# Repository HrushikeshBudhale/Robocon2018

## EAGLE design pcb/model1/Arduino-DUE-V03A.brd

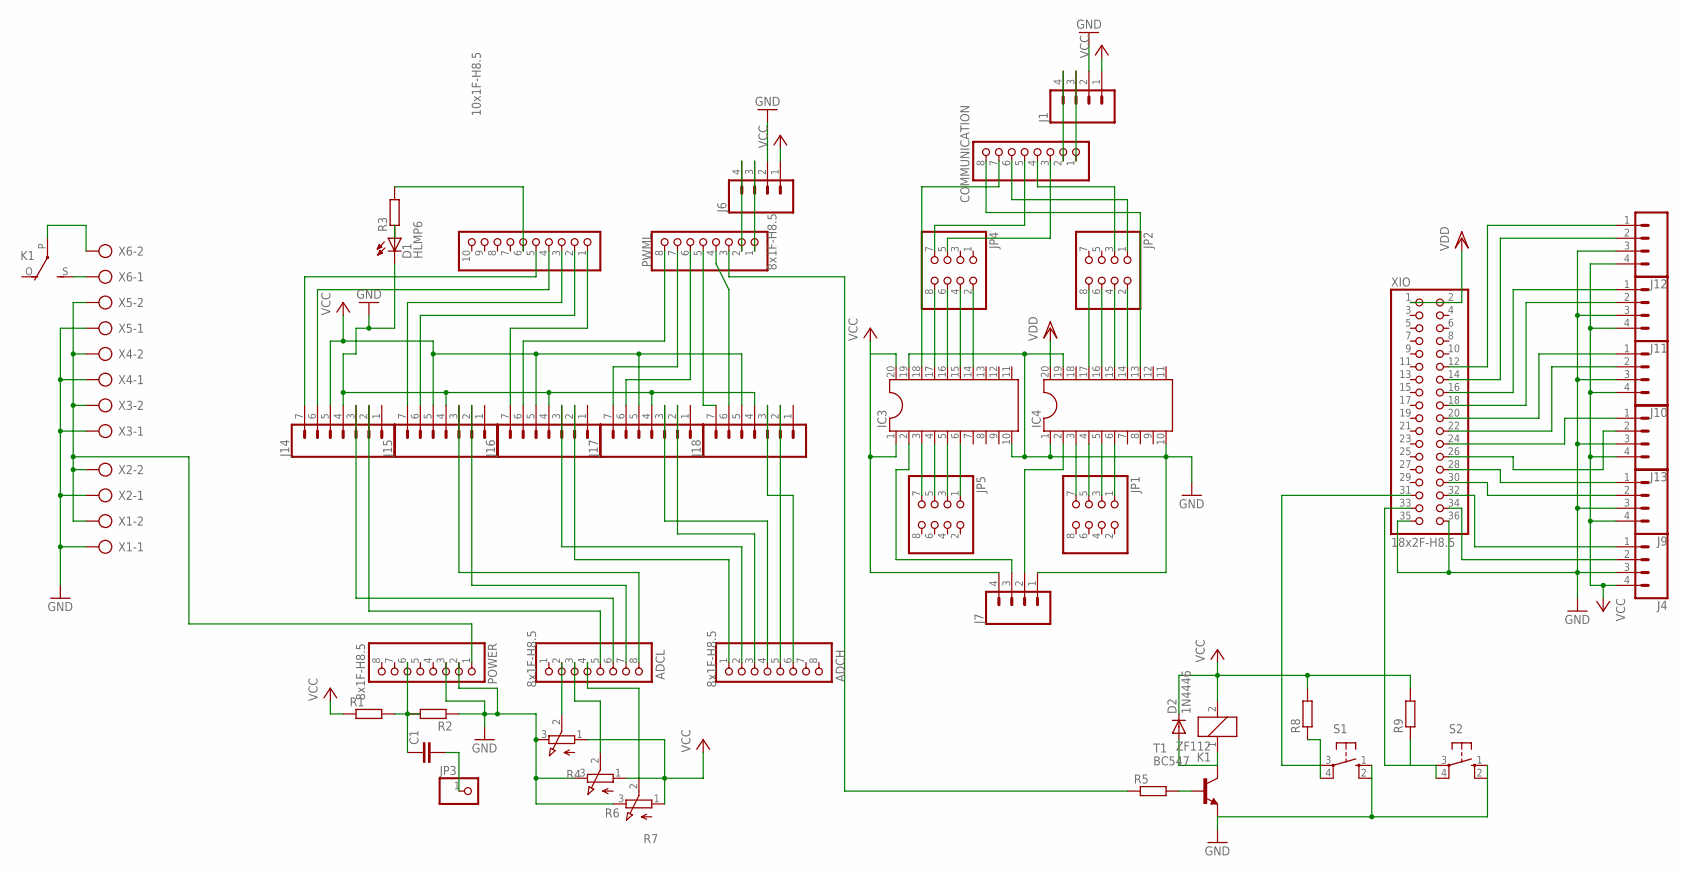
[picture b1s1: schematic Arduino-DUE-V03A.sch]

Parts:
ADCH: 8x1F-H8.5; 1X08
ADCL: 8x1F-H8.5; 1X08
C1: C-EU025-025X050; C025-025X050
COMMUNICATION: 8x1F-H8.5; 1X08
D1: HLMP6
D2: 1N4446; DO35-10
IC3, IC4: DIL20S; SOCKET-20
J1, J4, J6, J7, J9, J10, J11, J12, J13: CONN_04LONGPADS; 1X04_LONGPADS
J14, J15, J16, J17, J18: CONN_07LONGPADS; 1X07_LONGPADS
JP1, JP2, JP4, JP5: PINHD-2X4; 2X04
JP3: PINHD-1X1; 1X01
K1: ZF112
POWER: 8x1F-H8.5; 1X08
PWMH: 10x1F-H8.5; 1X10
PWML: 8x1F-H8.5; 1X08
R1, R2, R3, R5, R8, R9: R-EU_0204/7; 0204/7
R4, R6, R7: 3RP/1610N
S1, S2: 10-XX; B3F-10XX
T1: BC547; TO92
X1, X2, X3, X4, X5, X6: AK500/2
XIO: 18x2F-H8.5; 2X18

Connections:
GND: D1.K, IC3.10, IC3.19, IC4.1, IC4.10, IC4.19, J1.2, J4.3, J6.2, J7.1, J9.3, J10.3, J11.3, J12.3, J13.1, J13.3, J14.4, J15.4, J16.4, J17.4, J18.4, POWER.2, POWER.3, R2.1, R4.3 (E), R6.3 (E), R7.3 (E), S1.1 (S), S1.2 (S1), S2.1 (S), S2.2 (S1), T1.1 (E), X1.1, X2.1, X3.1, X4.1, X5.1, XIO.24, XIO.35, XIO.36
unnamed: J14.6, PWMH.4
unnamed: K1.S, X6.1
unnamed: K1.P, X6.2
unnamed: J4.2, XIO.34
unnamed: J15.6, PWMH.2
unnamed: J4.1, XIO.32
unnamed: COMMUNICATION.3, JP4.5
unnamed: J9.2, XIO.30
unnamed: J13.2, XIO.26
unnamed: POWER.1, X1.2, X2.2, X3.2, X4.2, X5.2
unnamed: J12.2, XIO.14
unnamed: J10.2, XIO.22
unnamed: J10.1, XIO.20
unnamed: J11.2, XIO.18
unnamed: J11.1, XIO.16
unnamed: J12.1, XIO.12
unnamed: R5.2, T1.2 (B)
unnamed: C1.2, JP3.1
unnamed: J16.7, PWMH.1
unnamed: J14.7, PWMH.5
unnamed: J15.7, PWMH.3
unnamed: J17.7, PWML.7
unnamed: J16.6, PWML.8
unnamed: J17.6, PWML.6
unnamed: J18.6, PWML.4
unnamed: ADCL.6, J14.3
unnamed: ADCL.5, J14.2
unnamed: ADCH.6, J18.3
unnamed: ADCH.5, J18.2
unnamed: ADCH.4, J17.3
unnamed: D1.A, R3.1
unnamed: ADCH.3, J17.2
unnamed: ADCH.2, J16.3
unnamed: ADCH.1, J16.2
unnamed: ADCL.8, J15.3
unnamed: PWMH.6, R3.2
unnamed: C1.1, POWER.6, R1.2, R2.2
unnamed: ADCL.7, J15.2
unnamed: J18.7, PWML.5
unnamed: COMMUNICATION.1, J1.3
unnamed: IC4.17, JP2.8
unnamed: IC4.16, JP2.6
unnamed: IC4.15, JP2.4
unnamed: IC4.14, JP2.2
unnamed: IC3.6, JP5.1
unnamed: IC3.5, JP5.3
unnamed: IC3.4, JP5.5
unnamed: IC3.3, JP5.7
unnamed: IC3.17, JP4.8
unnamed: IC3.16, JP4.6
unnamed: IC3.15, JP4.4
unnamed: IC3.14, JP4.2
unnamed: IC4.3, JP1.7
unnamed: IC4.4, JP1.5
unnamed: IC4.5, JP1.3
unnamed: IC4.6, JP1.1
unnamed: COMMUNICATION.7, IC3.18
unnamed: J6.4, PWML.2
unnamed: J6.3, PWML.1
unnamed: COMMUNICATION.6, JP2.1
unnamed: COMMUNICATION.2, J1.4
unnamed: COMMUNICATION.4, JP2.3
unnamed: COMMUNICATION.5, JP4.7
unnamed: IC3.2, J7.3
unnamed: IC4.2, J7.2
unnamed: D2.A, K1.1, T1.3 (C)
unnamed: R8.1, S1.3, S1.4 (P1), XIO.31
unnamed: ADCL.2, R4.2 (S)
unnamed: ADCL.4, R7.2 (S)
unnamed: ADCL.3, R6.2 (S)
unnamed: PWML.3, R5.1
unnamed: R9.1, S2.3, S2.4 (P1), XIO.33
unnamed: J9.1, XIO.28
unnamed: COMMUNICATION.8, IC4.13
VCC: D2.C, IC3.1, IC3.20, J1.1, J4.4, J6.1, J7.4, J9.4, J10.4, J11.4, J12.4, J13.4, J14.5, J15.5, J16.5, J17.5, J18.5, K1.2, R1.1, R4.1 (A), R6.1 (A), R7.1 (A), R8.2, R9.2
VDD: IC4.20, XIO.1, XIO.2

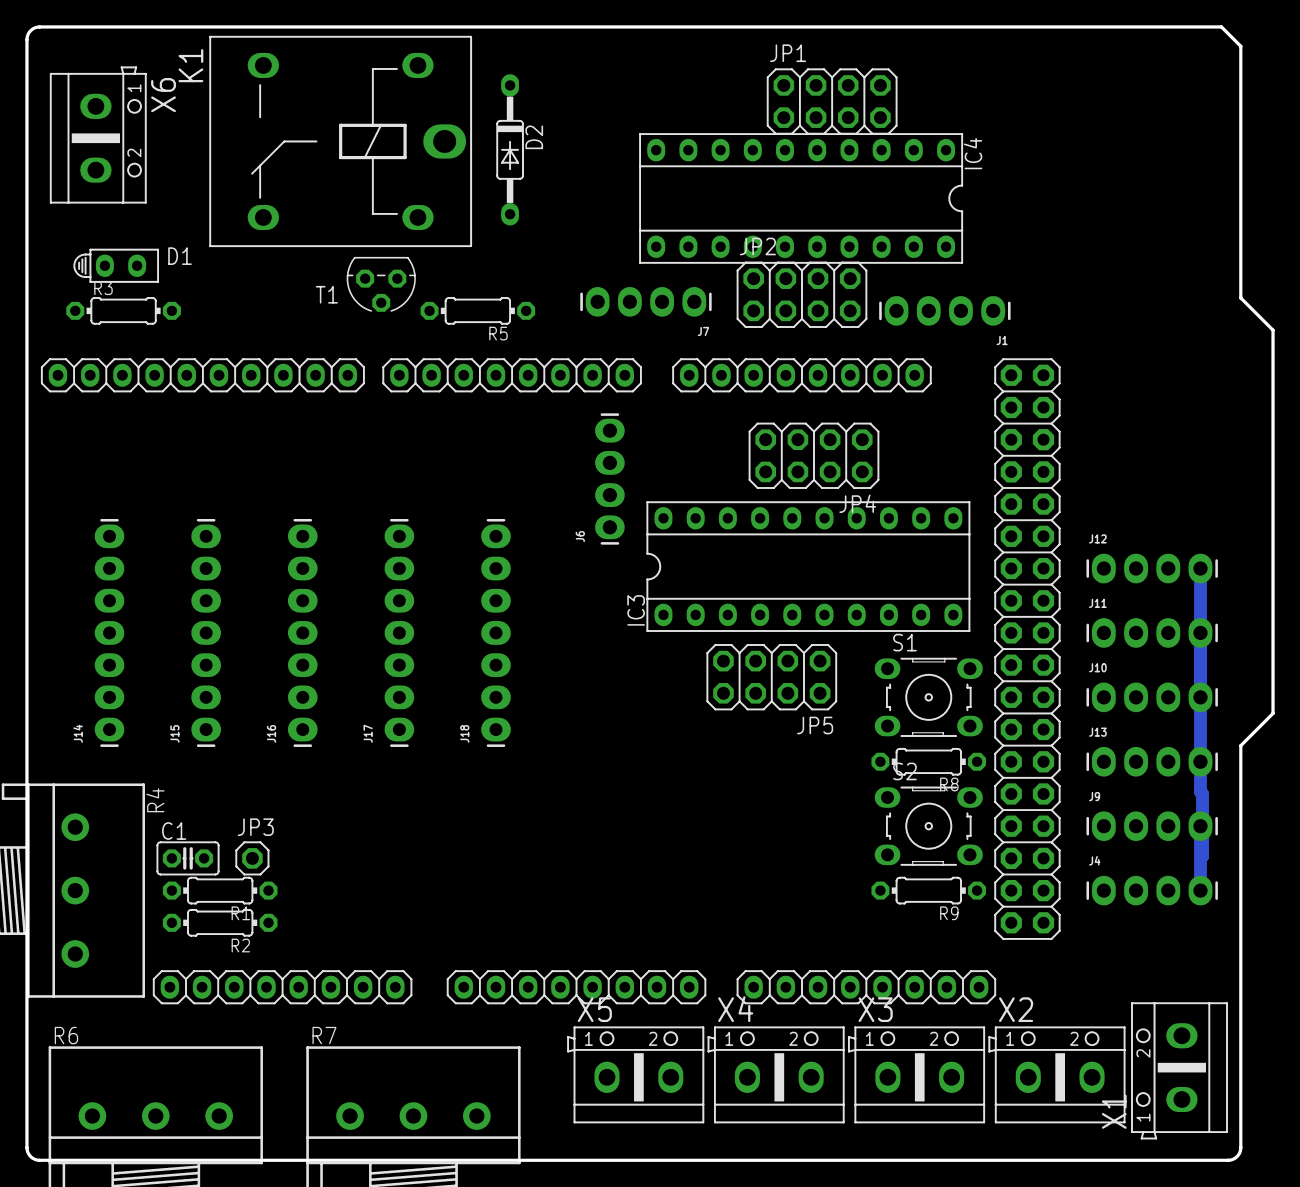
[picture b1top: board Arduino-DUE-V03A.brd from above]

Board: 2 copper layers, 98.3 x 89.4 mm, 50 parts (0 on the bottom side), 77 nets.

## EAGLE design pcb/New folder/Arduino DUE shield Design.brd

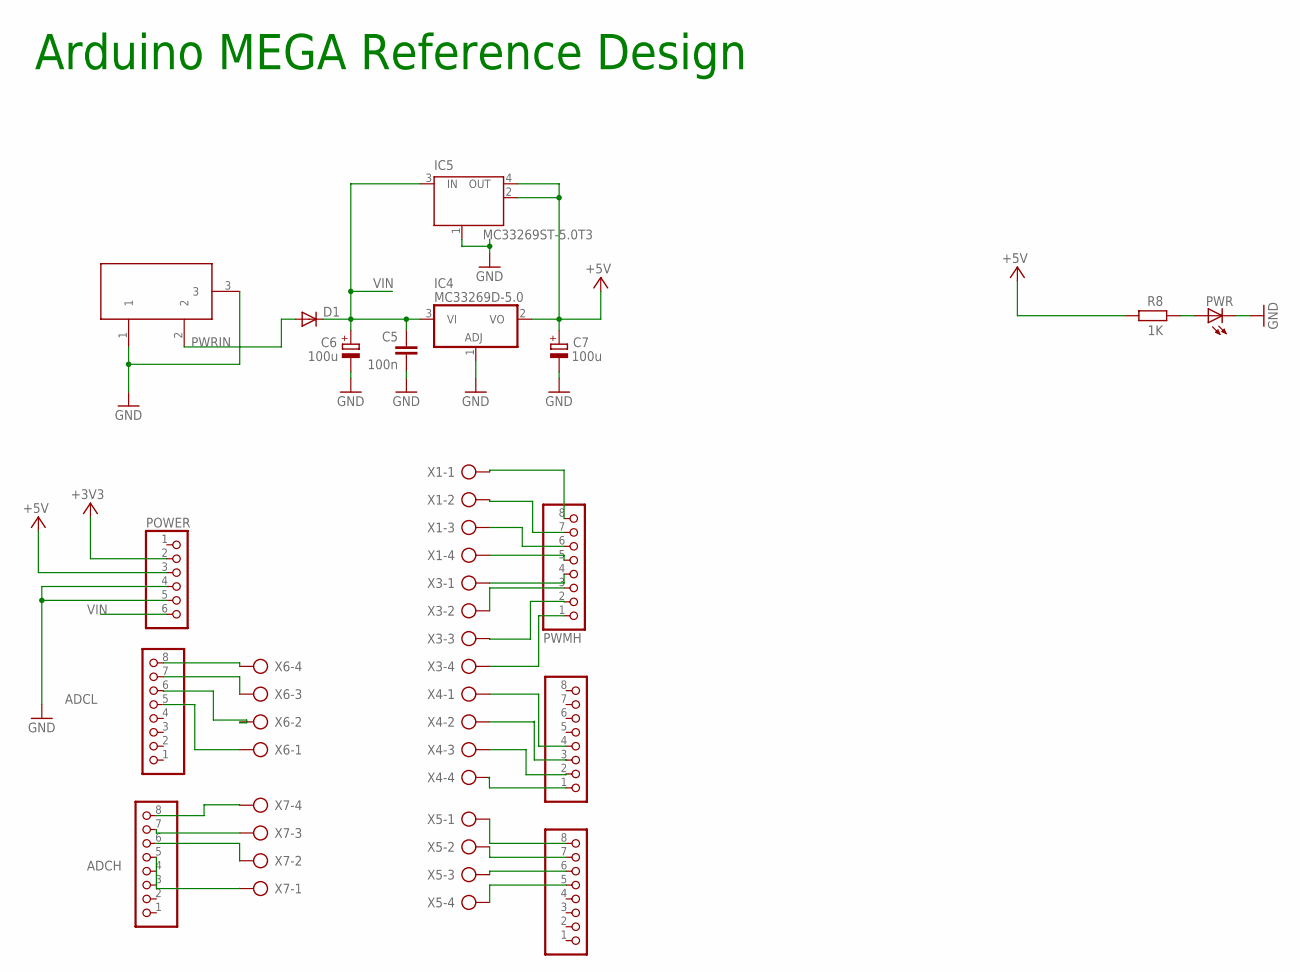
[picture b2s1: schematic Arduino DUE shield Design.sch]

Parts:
ADCH: PINHD-1X8; 1X08
ADCL: PINHD-1X8; 1X08
C5: 100n; C0805RND
C6, C7: 100u; SMC_D
COMMUNICATION: PINHD-1X8; 1X08
D1: DIODE-SMB; SMB
IC4: MC33269D-5.0; DPACK
IC5: MC33269ST-5.0T3; SOT223
POWER: PINHD-1X6; 1X06
PWMH: PINHD-1X8; 1X08
PWML: PINHD-1X8; 1X08
PWR: LED0805ROUND; 0805RND
R8: 1K; R0805RND
X1, X3, X4, X5, X6, X7: AK500/4
X2: DC21MMX; DC-21MM

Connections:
+3V3: POWER.2
+5V: C7.+, IC4.2 (VO), IC5.2 (OUT), IC5.4 (OUT), POWER.3, R8.1
GND: C5.2, C6.-, C7.-, IC4.1 (ADJ), IC5.1 (GND/ADJ), POWER.4, POWER.5, PWR.P$2 (C), X2.1, X2.3
unnamed: ADCL.8, X6.4
unnamed: ADCL.7, X6.3
unnamed: PWR.P$1 (A), R8.2
unnamed: ADCL.6, X6.2
unnamed: ADCL.5, X6.1
unnamed: ADCH.8, X7.4
unnamed: ADCH.7, X7.3
unnamed: ADCH.6, X7.2
unnamed: ADCH.5, X7.1
unnamed: COMMUNICATION.8, X5.1
unnamed: COMMUNICATION.7, X5.2
unnamed: COMMUNICATION.6, X5.3
unnamed: COMMUNICATION.5, X5.4
unnamed: PWML.1, X4.4
unnamed: PWML.2, X4.3
unnamed: PWML.3, X4.2
unnamed: PWML.4, X4.1
unnamed: PWMH.1, X3.4
unnamed: PWMH.2, X3.3
unnamed: PWMH.3, X3.2
unnamed: PWMH.4, X3.1
unnamed: PWMH.5, X1.4
unnamed: PWMH.6, X1.3
unnamed: PWMH.7, X1.2
unnamed: PWMH.8, X1.1
PWRIN: D1.A, X2.2
VIN: C5.1, C6.+, D1.C, IC4.3 (VI), IC5.3 (IN), POWER.6

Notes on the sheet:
Arduino MEGA Reference Design

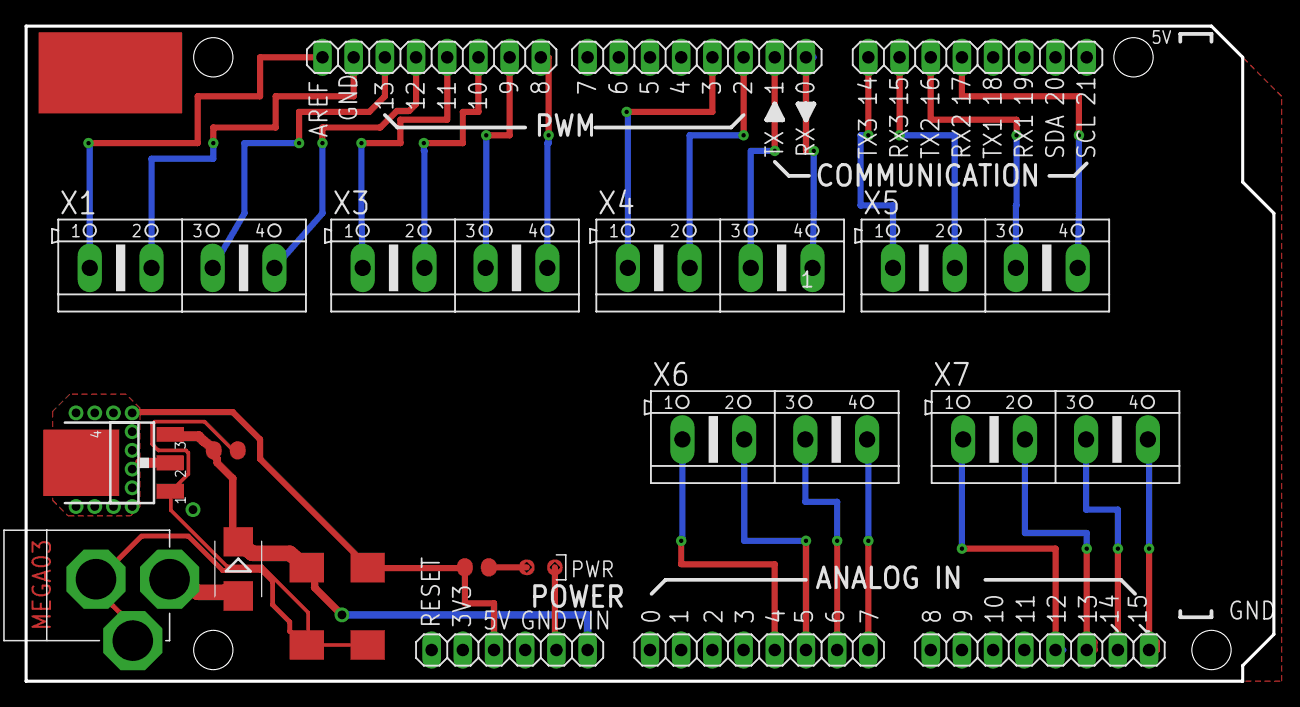
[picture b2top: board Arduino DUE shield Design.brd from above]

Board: 2 copper layers, 101.6 x 53.3 mm, 21 parts (0 on the bottom side), 29 nets.

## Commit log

2018-02-01 add pos_adj_test, add myPID.setParam to UI_forTesting
2018-02-04 complete state_machine, add ldr_test, add pos_adjust_test for drive
2018-02-04 add const_speed
2018-02-12 add complete_machine
2018-02-17 add machine without PID and lidar test
2018-03-14 closing commit
2018-03-14 'docs'

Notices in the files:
parts and their libraries:
SparkFun-Connectors: Licensing: Creative Commons ShareAlike 4.0 International - https://creativecommons.org/licenses/by-sa/4.0
